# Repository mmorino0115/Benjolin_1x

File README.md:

# Benjolin_1x
Benjolin_1x KiCAD data. I designed this PCB based on the schematics of forestcaver's Benjolin 1.6. Then added some additional ideas from Jolin Lab's BE2N. I am really grateful to Rob Hordijk, who designed the original Benjolin. Following the original Benjolin design intent, this PCB is for personal, non-commercial use only.

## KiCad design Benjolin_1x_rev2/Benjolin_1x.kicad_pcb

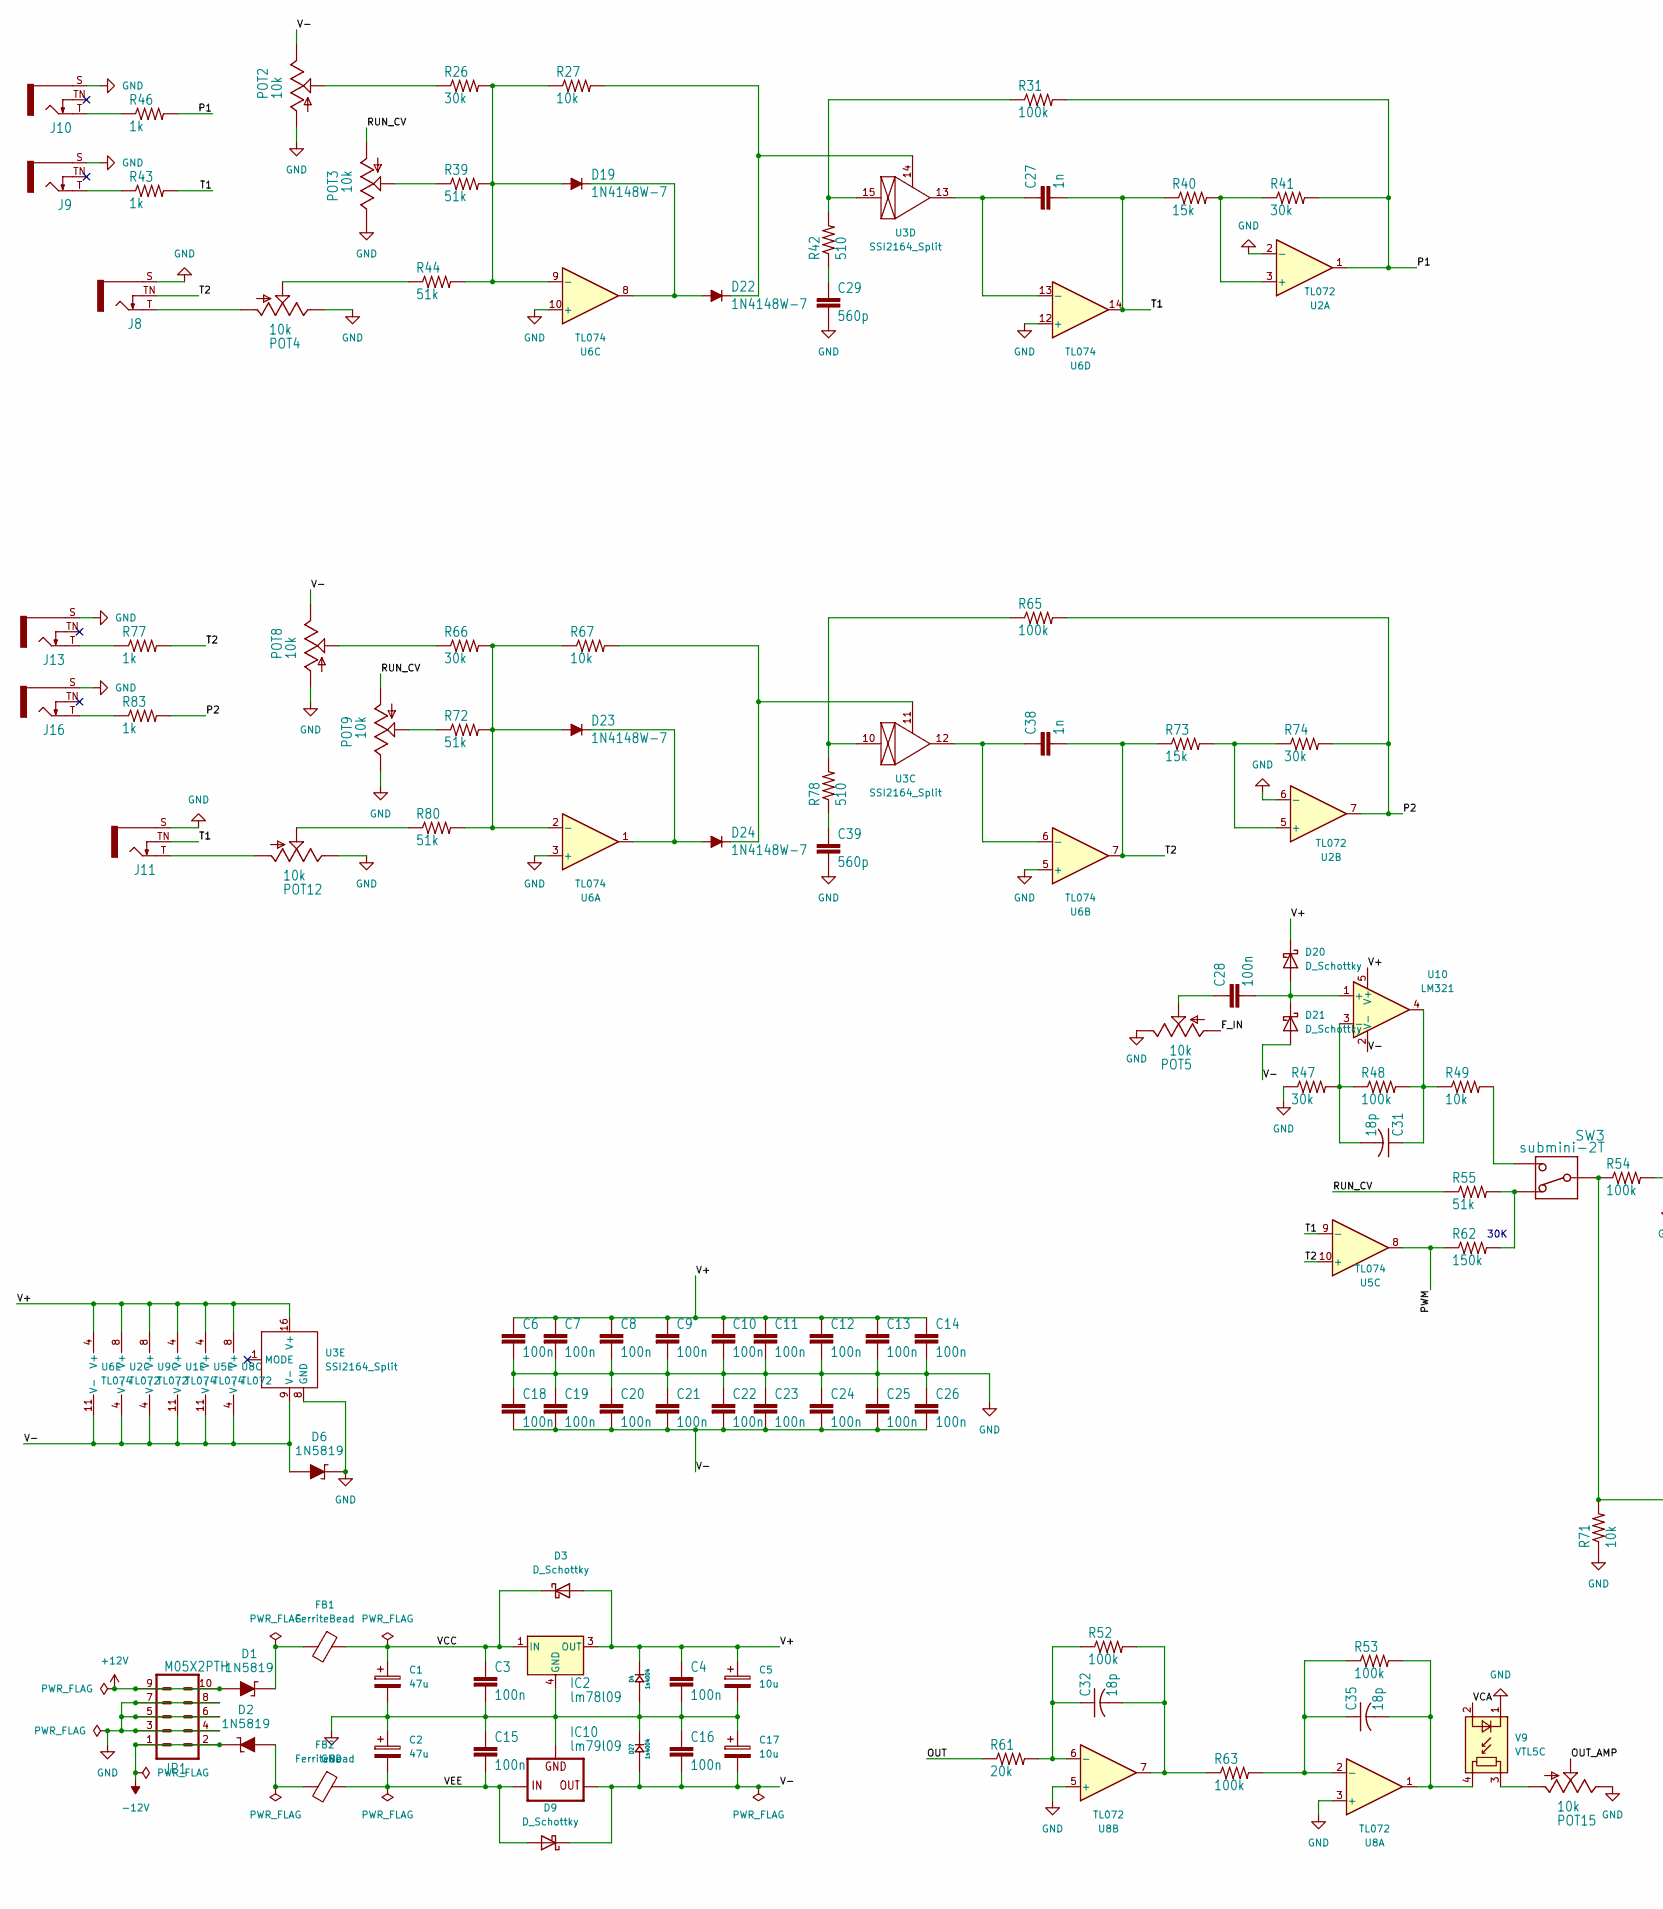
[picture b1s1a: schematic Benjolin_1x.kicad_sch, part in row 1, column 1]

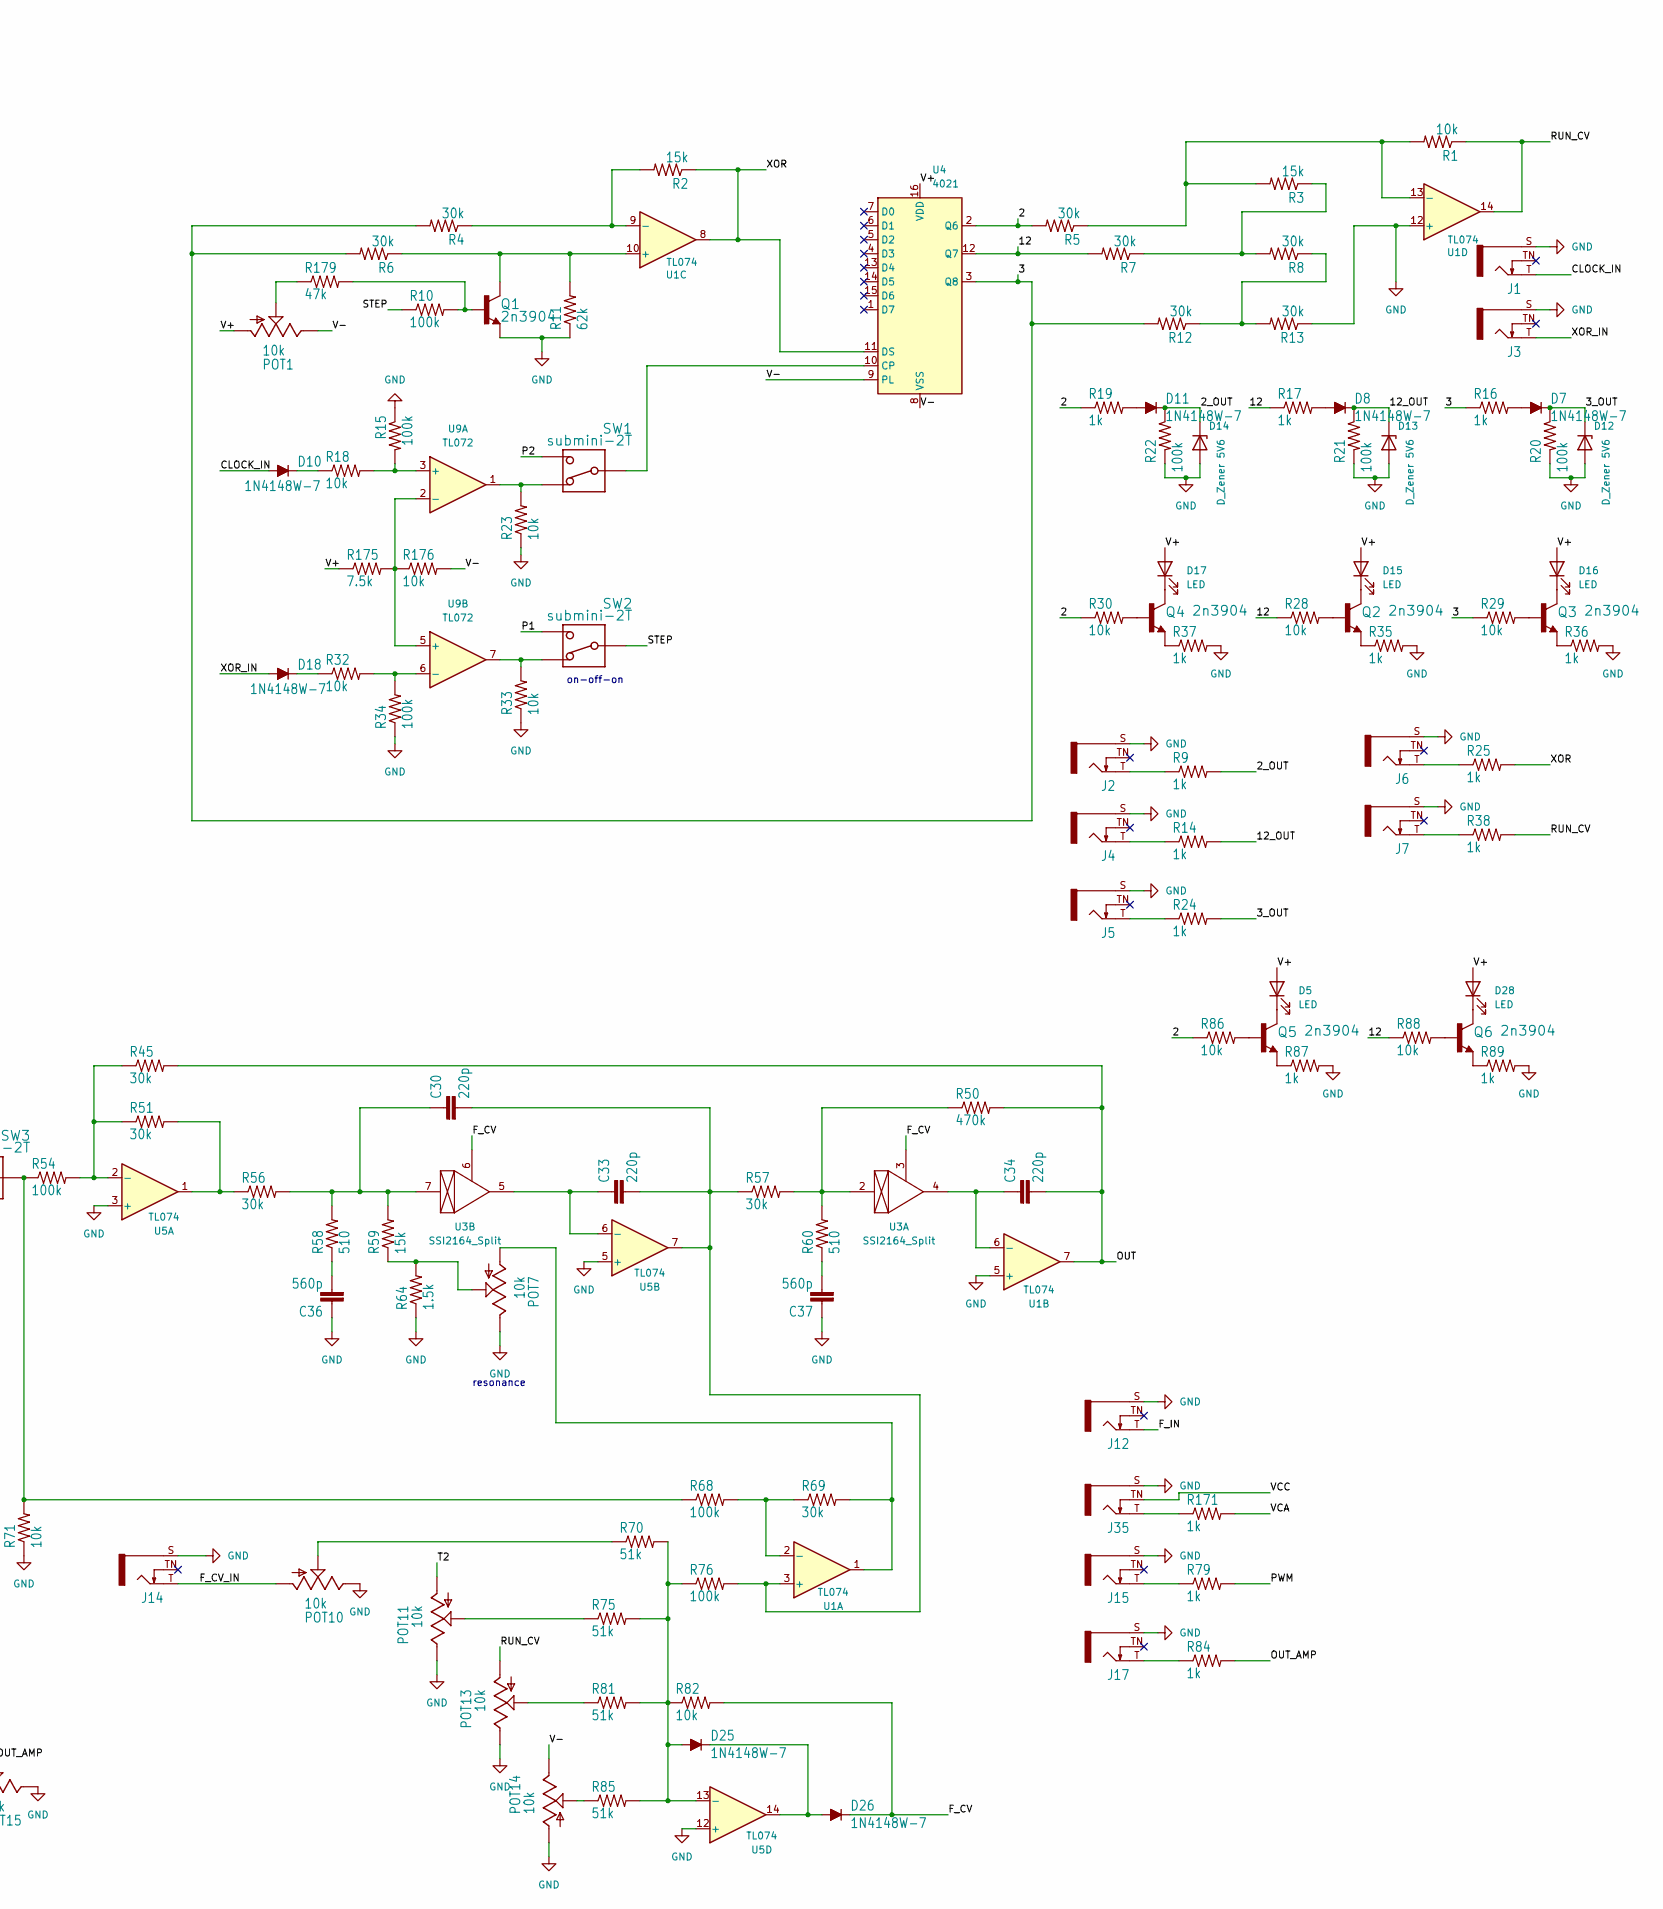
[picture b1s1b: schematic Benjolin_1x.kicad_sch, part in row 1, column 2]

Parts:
C1, C2: 47u; CP_Elec_5x4.5
C3, C4, C6, C7, C8, C9, C10, C11, C12, C13, C14, C15, C16, C18, C19, C20, C21, C22, C23, C24, C25, C26, C28: 100n; C_0603_1608Metric_Pad1.08x0.95mm_HandSolder
C5, C17: 10u; CP_Elec_4x5.4
C27, C38: 1n; C_0603_1608Metric_Pad1.08x0.95mm_HandSolder
C29, C36, C37, C39: 560p; C_0603_1608Metric_Pad1.08x0.95mm_HandSolder
C30, C33, C34: 220p; C_0603_1608Metric_Pad1.08x0.95mm_HandSolder
C31, C32, C35: 18p; C_0603_1608Metric_Pad1.08x0.95mm_HandSolder
D1, D2, D6: 1N5819; SOD-123; MPN 1N5819; Digi-Key_PN 1N5819FSCT-ND
D3, D9, D20, D21: D_Schottky; D_SMA
D4, D27: 1n4004; D_SMA_Handsoldering
D5, D15, D16, D17, D28: LED; LED_D3.0mm
D7, D8, D10, D11, D18, D19, D22, D23, D24, D25, D26: 1N4148W-7; D_SOD-123F
D12, D13, D14: D_Zener 5V6; D_MiniMELF_Handsoldering
FB1, FB2: FerriteBead; L_0603_1608Metric
IC2: lm78l09; TO-252-3
IC10: lm79l09; SOT-89-3
J1, J2, J3, J4, J5, J6, J7, J8, J9, J10, J11, J12, J13, J14, J15, J16, J17, J35: PJ301_THONKICONN6; AudioJack_3.5mm
JP1: M05X2PTH; IDC-Header_2x05_P2.54mm_Vertical
POT1, POT2, POT3, POT4, POT5, POT7, POT8, POT9, POT10, POT11, POT12, POT13, POT14, POT15: 10k; Potentiometer_Alps_RK09K_Single_Vertical
Q1, Q2, Q3, Q4, Q5, Q6: 2n3904; SOT-23-3
R1, R18, R23, R27, R28, R29, R30, R32, R33, R49, R67, R71, R82, R86, R88, R176: 10k; R_0603_1608Metric_Pad0.98x0.95mm_HandSolder
R2, R3, R40, R59, R73: 15k; R_0603_1608Metric_Pad0.98x0.95mm_HandSolder
R4, R5, R6, R7, R8, R12, R13, R26, R41, R45, R47, R51, R56, R57, R66, R69, R74: 30k; R_0603_1608Metric_Pad0.98x0.95mm_HandSolder
R9, R14, R16, R17, R19, R24, R25, R35, R36, R37, R38, R43, R46, R77, R79, R83, R84, R87, R89, R171: 1k; R_0603_1608Metric_Pad0.98x0.95mm_HandSolder
R10, R15, R20, R21, R22, R31, R34, R48, R52, R53, R54, R63, R65, R68, R76: 100k; R_0603_1608Metric_Pad0.98x0.95mm_HandSolder
R11: 62k; R_0603_1608Metric_Pad0.98x0.95mm_HandSolder
R39, R44, R55, R70, R72, R75, R80, R81, R85: 51k; R_0603_1608Metric_Pad0.98x0.95mm_HandSolder
R42, R58, R60, R78: 510; R_0603_1608Metric_Pad0.98x0.95mm_HandSolder
R50: 470k; R_0603_1608Metric_Pad0.98x0.95mm_HandSolder
R61: 20k; R_0603_1608Metric_Pad0.98x0.95mm_HandSolder
R62: 150k; R_0603_1608Metric_Pad0.98x0.95mm_HandSolder
R64: 1.5k; R_0603_1608Metric_Pad0.98x0.95mm_HandSolder
R175: 7.5k; R_0603_1608Metric_Pad0.98x0.95mm_HandSolder
R179: 47k; R_0603_1608Metric_Pad0.98x0.95mm_HandSolder
SW1, SW2, SW3: submini-2T; SPDT
U1, U5, U6: TL074; TSSOP-14_4.4x5mm_P0.65mm
U2, U8, U9: TL072; TSSOP-8_4.4x3mm_P0.65mm
U3: SSI2164_Split; SOIC-16_3.9x9.9mm_P1.27mm
U4: 4021; SOIC-16_3.9x9.9mm_P1.27mm
U10: LM321; SOT-23-5
V9: VTL5C; PerkinElmer_VTL5C

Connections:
+12V: D1.A, JP1.9, JP1.10
-12V: D2.K, JP1.1, JP1.2
/2: R5.2, R19.1, R30.1, R86.1, U4.2 (Q6)
/2_OUT: D11.1, D14.1 (K), R9.2, R22.1
/3: R4.2, R6.2, R12.2, R16.1, R29.1, U4.3 (Q8)
/3_OUT: D7.1, D12.1 (K), R20.1, R24.2
/12: R7.2, R17.1, R28.1, R88.1, U4.12 (Q7)
/12_OUT: D8.1, D13.1 (K), R14.2, R21.1
/CLOCK_IN: D10.2, J1.T
/F_CV: D26.1, R82.2, U3.3, U3.6
/F_CV_IN: J14.T, POT10.3
/F_IN: J12.T, POT5.3
/OUT: C34.2, R45.2, R50.2, R61.1, U1.7
/OUT_AMP: POT15.2, R84.2
/P1: R31.2, R41.2, R46.2, SW2.1, U2.1
/P2: R65.2, R74.2, R83.2, SW1.1, U2.7
/PWM: R62.1, R79.2, U5.8
/RUN_CV: POT3.3, POT9.3, POT13.3, R1.1, R38.2, R55.1, U1.14
/STEP: R10.1, SW2.2
/T1: C27.2, J11.TN, R40.1, R43.2, U5.9 (-), U6.14
/T2: C38.2, J8.TN, POT11.3, R73.1, R77.2, U5.10 (+), U6.7
/V+: C4.1, C5.1, C6.1, C7.1, C8.1, C9.1, C10.1, C11.1, C12.1, C13.1, C14.1, D3.2 (A), D4.2 (-), D5.2 (A), D15.2 (A), D16.2 (A), D17.2 (A), D20.1 (K), D28.2 (A), IC2.3 (OUT), POT1.3, R175.1, U1.4 (V+), U2.8 (V+), U3.16 (V+), U4.16 (VDD), U5.4 (V+), U6.4 (V+), U8.8 (V+), U9.8 (V+), U10.5 (V+)
/V-: C16.2, C17.2, C18.2, C19.2, C20.2, C21.2, C22.2, C23.2, C24.2, C25.2, C26.2, D6.A, D9.1 (K), D21.2 (A), D27.1 (+), IC10.3 (OUT), POT1.1, POT2.1, POT8.1, POT14.1, R176.2, U1.11 (V-), U2.4 (V-), U3.9 (V-), U4.8 (VSS), U4.9 (PL), U5.11 (V-), U6.11 (V-), U8.4 (V-), U9.4 (V-), U10.2 (V-)
/VCA: R171.2, V9.2 (+)
/VCC: C1.1, C3.1, D3.1 (K), FB1.1, IC2.1 (IN), J35.TN
/VEE: C2.2, C15.2, D9.2 (A), FB2.1, IC10.2
/XOR: R2.1, R25.2, U1.8, U4.11 (DS)
/XOR_IN: D18.2, J3.T
GND: C1.2, C2.1, C3.2, C4.2, C5.2, C6.2, C7.2, C8.2, C9.2, C10.2, C11.2, C12.2, C13.2, C14.2, C15.1, C16.1, C17.1, C18.1, C19.1, C20.1, C21.1, C22.1, C23.1, C24.1, C25.1, C26.1, C29.2, C36.1, C37.1, C39.2, D4.1 (+), D6.K, D12.2 (A), D13.2 (A), D14.2 (A), D27.2 (-), IC2.4 (GND), IC10.1 (GND), J1.S, J2.S, J3.S, J4.S, J5.S, J6.S, J7.S, J8.S, J9.S, J10.S, J11.S, J12.S, J13.S, J14.S, J15.S, J16.S, J17.S, J35.S, JP1.3, JP1.4, JP1.5, JP1.6, JP1.7, JP1.8, POT2.3, POT3.1, POT4.1, POT5.1, POT7.1, POT8.3, POT9.1, POT10.1, POT11.1, POT12.1, POT13.1, POT14.3, POT15.1, Q1.2 (E), R11.1, R13.1, R15.1, R20.2, R21.2, R22.2, R23.1, R33.1, R34.1, R35.2, R36.2, R37.2, R47.1, R64.1, R71.1, R87.2, R89.2, U1.5 (+), U1.12 (+), U2.2 (-), U2.6 (-), U3.8 (GND), U5.3 (+), U5.5 (+), U5.12 (+), U6.3 (+), U6.5 (+), U6.10 (+), U6.12 (+), U8.3 (+), U8.5 (+), V9.1 (-)
unnamed: C28.1, POT5.2
unnamed: C29.1, R42.1
unnamed: C30.1, R56.2, R58.2, R59.2, U3.7
unnamed: C31.1, R48.2, R49.1, U10.4
unnamed: C32.2, R52.2, R63.1, U8.7
unnamed: C35.2, R53.2, U8.1, V9.4
unnamed: C36.2, R58.1
unnamed: C37.2, R60.1
unnamed: C39.1, R78.1
unnamed: D1.K, FB1.2
unnamed: D2.A, FB2.2
unnamed: D5.1 (K), Q5.3 (C)
unnamed: D7.2, R16.2
unnamed: D8.2, R17.2
unnamed: D10.1, R18.1
unnamed: D11.2, R19.2
unnamed: D15.1 (K), Q2.3 (C)
unnamed: D16.1 (K), Q3.3 (C)
unnamed: D17.1 (K), Q4.3 (C)
unnamed: D18.1, R32.1
unnamed: D19.1, D22.2, U6.8
unnamed: C28.2, D20.2 (A), D21.1 (K), U10.1 (+)
unnamed: D22.1, R27.2, U3.14
unnamed: D23.1, D24.2, U6.1
unnamed: D24.1, R67.2, U3.11
unnamed: D25.1, D26.2, U5.14
unnamed: D28.1 (K), Q6.3 (C)
unnamed: J2.T, R9.1
unnamed: J4.T, R14.1
unnamed: J5.T, R24.1
unnamed: J6.T, R25.1
unnamed: J7.T, R38.1
unnamed: J8.T, POT4.3
unnamed: J9.T, R43.1
unnamed: J10.T, R46.1
unnamed: J11.T, POT12.3
unnamed: J13.T, R77.1
unnamed: J15.T, R79.1
unnamed: J16.T, R83.1
unnamed: J17.T, R84.1
unnamed: J35.T, R171.1
unnamed: POT1.2, R179.1
unnamed: POT2.2, R26.1
unnamed: POT3.2, R39.1
unnamed: POT4.2, R44.1
unnamed: POT7.2, R59.1, R64.2
unnamed: POT7.3, R69.2, U1.1
unnamed: POT8.2, R66.1
unnamed: POT9.2, R72.1
unnamed: POT10.2, R70.1
unnamed: POT11.2, R75.1
unnamed: POT12.2, R80.1
unnamed: POT13.2, R81.1
unnamed: POT14.2, R85.1
unnamed: POT15.3, V9.3
unnamed: Q1.1 (B), R10.2, R179.2
unnamed: Q1.3 (C), R6.1, R11.2, U1.10 (+)
unnamed: Q2.1 (B), R28.2
unnamed: Q2.2 (E), R35.1
unnamed: Q3.1 (B), R29.2
unnamed: Q3.2 (E), R36.1
unnamed: Q4.1 (B), R30.2
unnamed: Q4.2 (E), R37.1
unnamed: Q5.1 (B), R86.2
unnamed: Q5.2 (E), R87.1
unnamed: Q6.1 (B), R88.2
unnamed: Q6.2 (E), R89.1
unnamed: R3.1, R7.1, R8.2
unnamed: R8.1, R12.1, R13.2
unnamed: R23.2, SW1.3, U9.1
unnamed: R31.1, R42.2, U3.15
unnamed: R33.2, SW2.3, U9.7
unnamed: R49.2, SW3.1
unnamed: R50.1, R57.2, R60.2, U3.2
unnamed: R51.2, R56.1, U5.1
unnamed: R54.1, R68.1, R71.2, SW3.2
unnamed: R55.2, R62.2, SW3.3
unnamed: R65.1, R78.2, U3.10
unnamed: C30.2, C33.2, R57.1, R76.2, U1.3 (+), U5.7
unnamed: R68.2, R69.1, U1.2 (-)
unnamed: C34.1, U1.6 (-), U3.4
unnamed: R2.2, R4.1, U1.9 (-)
unnamed: R1.2, R3.2, R5.1, U1.13 (-)
unnamed: R40.2, R41.1, U2.3 (+)
unnamed: R73.2, R74.1, U2.5 (+)
unnamed: SW1.2, U4.10 (CP)
unnamed: R45.1, R51.1, R54.2, U5.2 (-)
unnamed: C33.1, U3.5, U5.6 (-)
unnamed: D25.2, R70.2, R75.2, R76.1, R81.2, R82.1, R85.2, U5.13 (-)
unnamed: D23.2, R66.2, R67.1, R72.2, R80.2, U6.2 (-)
unnamed: C38.1, U3.12, U6.6 (-)
unnamed: D19.2, R26.2, R27.1, R39.2, R44.2, U6.9 (-)
unnamed: C27.1, U3.13, U6.13 (-)
unnamed: C35.1, R53.1, R63.2, U8.2 (-)
unnamed: C32.1, R52.1, R61.2, U8.6 (-)
unnamed: R15.2, R18.2, U9.3 (+)
unnamed: R175.2, R176.1, U9.2 (-), U9.5 (+)
unnamed: R32.2, R34.2, U9.6 (-)
unnamed: C31.2, R47.2, R48.1, U10.3 (-)

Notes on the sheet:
on-off-on
resonance
30K

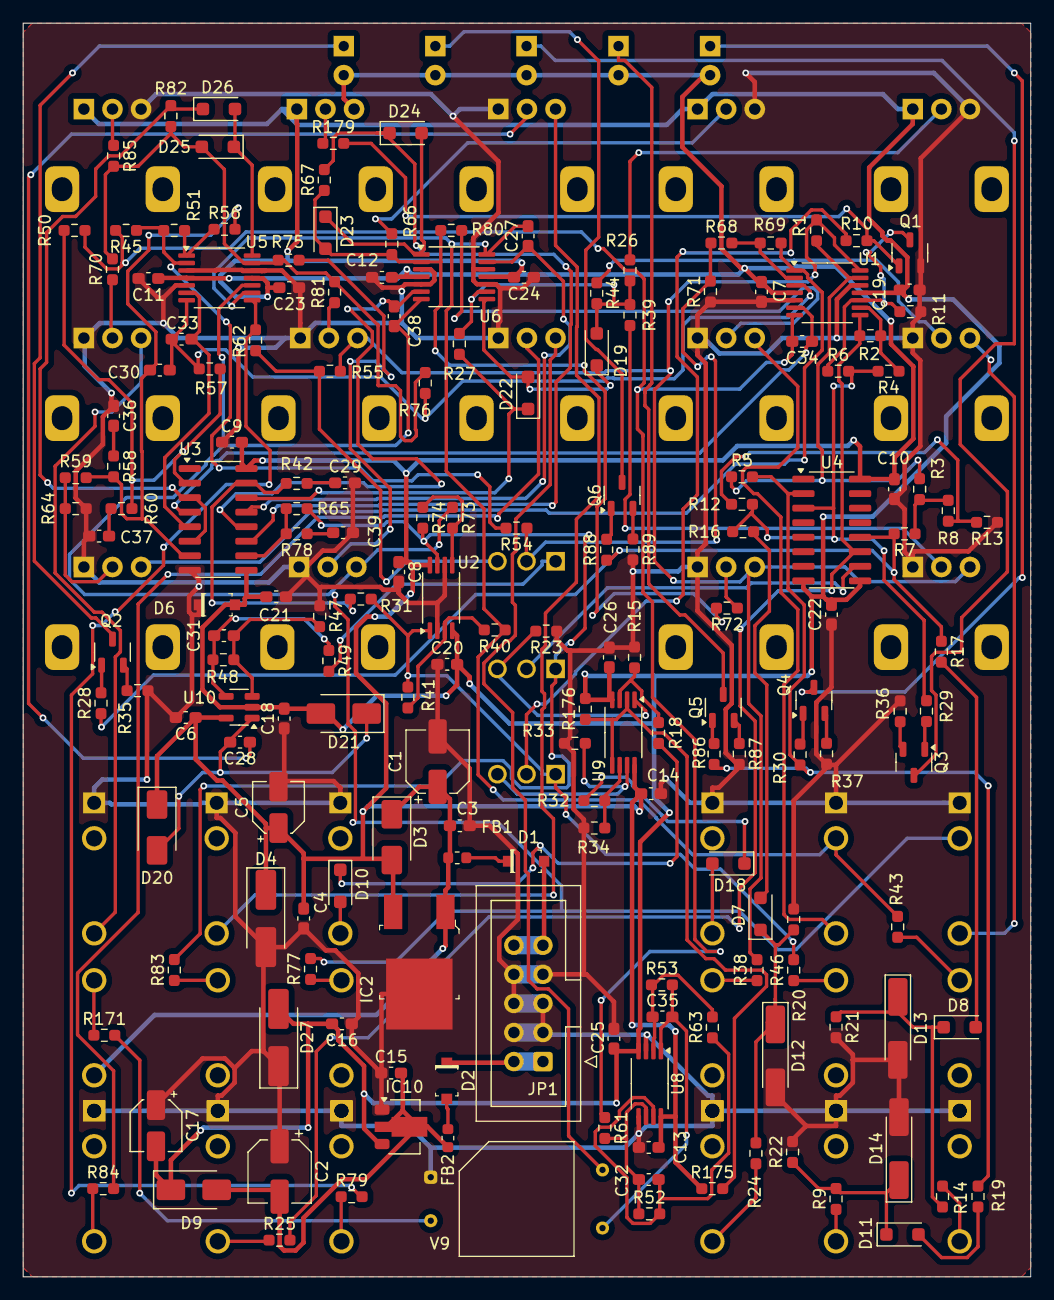
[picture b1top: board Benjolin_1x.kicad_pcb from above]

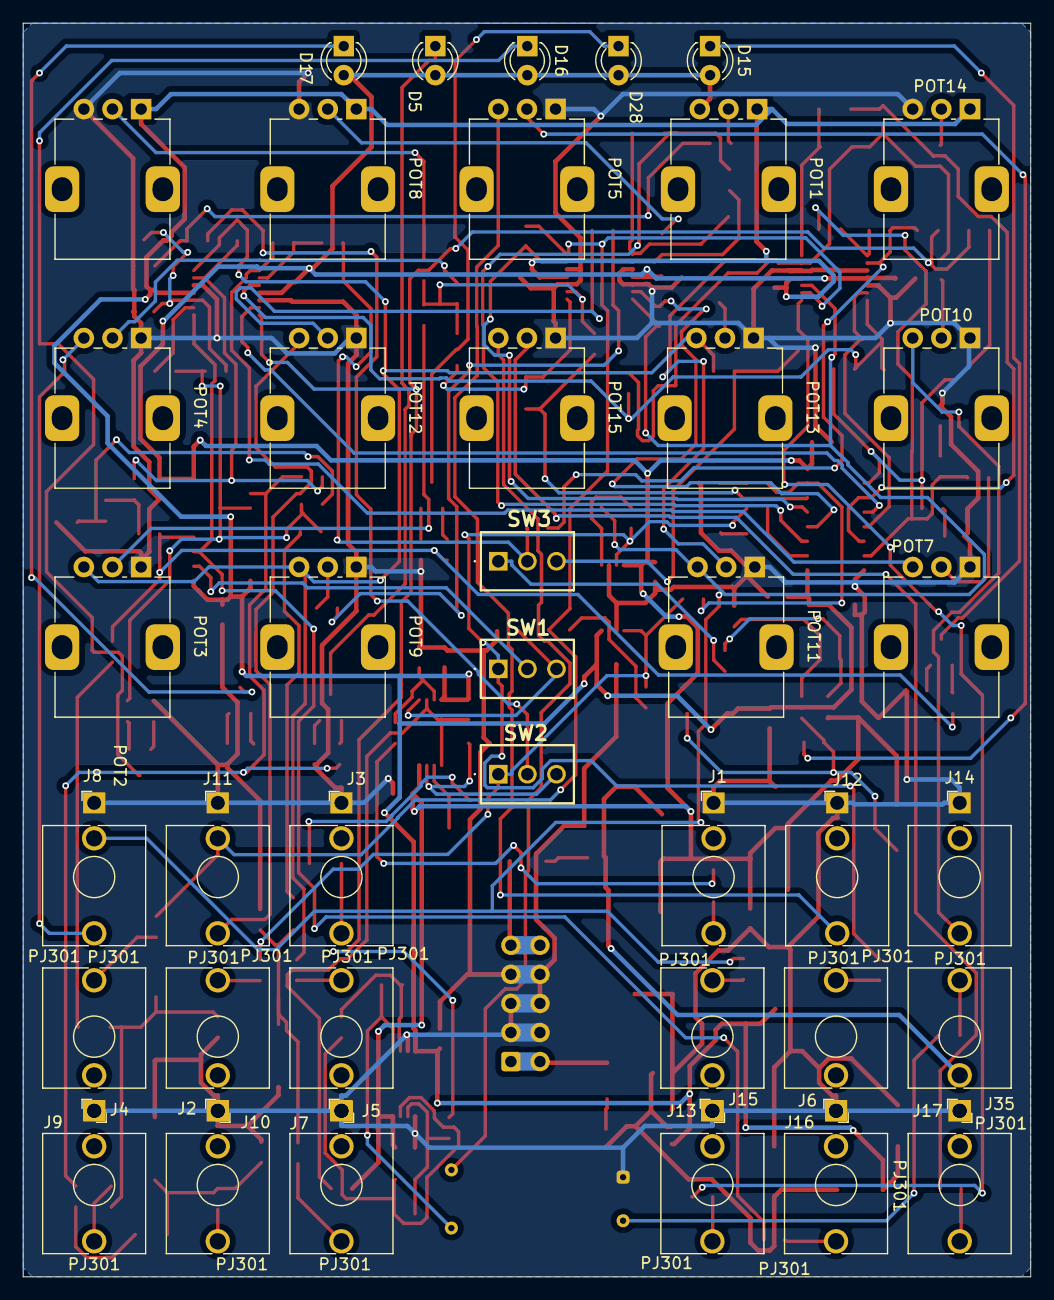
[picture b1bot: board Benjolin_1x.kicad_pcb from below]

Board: 2 copper layers, 88.0 x 109.5 mm, 216 parts (40 on the bottom side), 128 nets.

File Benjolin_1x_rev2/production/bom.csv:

Designator,Footprint,Quantity,Value,LCSC Part #
"C1, C2",CP_Elec_5x4.5,2,47u,
"C10, C11, C12, C13, C14, C15, C16, C18, C19, C20, C21, C22, C23, C24, C25, C26, C28, C3, C4, C6, C7, C8, C9",0603,23,100n,
"C17, C5",CP_Elec_4x5.4,2,10u,
"C27, C38",0603,2,1n,
"C29, C36, C37, C39",0603,4,560p,
"C30, C33, C34",0603,3,220p,
"C31, C32, C35",0603,3,18p,
"D1, D2, D6",SOD-123,3,1N5819,1N5819
"D10, D11, D18, D19, D22, D23, D24, D25, D26, D7, D8",D_SOD-123F,11,1N4148W-7,
"D12, D13, D14",D_MiniMELF_Handsoldering,3,D_Zener 5V6,
"D15, D16, D17, D28, D5",LED_D3.0mm,5,LED,
"D20, D21, D3, D9",D_SMA,4,D_Schottky,
"D27, D4",D_SMA_Handsoldering,2,1n4004,
"FB1, FB2",0603,2,FerriteBead,
IC10,SOT-89-3,1,lm79l09,
IC2,TO-252-3,1,lm78l09,
"J1, J10, J11, J12, J13, J14, J15, J16, J17, J2, J3, J35, J4, J5, J6, J7, J8, J9",AudioJack_3.5mm,18,PJ301,
JP1,IDC-Header_2x05_P2.54mm_Vertical,1,M05X2PTH,
"POT1, POT10, POT11, POT12, POT13, POT14, POT15, POT2, POT3, POT4, POT5, POT7, POT8, POT9",Potentiometer_Alps_RK09K_Single_Vertical,14,10k,
"Q1, Q2, Q3, Q4, Q5, Q6",SOT-23-3,6,2n3904,
"R1, R176, R18, R23, R27, R28, R29, R30, R32, R33, R49, R67, R71, R82, R86, R88",0603,16,10k,
"R10, R15, R20, R21, R22, R31, R34, R48, R52, R53, R54, R63, R65, R68, R76",0603,15,100k,
R11,0603,1,62k,
"R12, R13, R26, R4, R41, R45, R47, R5, R51, R56, R57, R6, R66, R69, R7, R74, R8",0603,17,30k,
"R14, R16, R17, R171, R19, R24, R25, R35, R36, R37, R38, R43, R46, R77, R79, R83, R84, R87, R89, R9",0603,20,1k,
R175,0603,1,7.5k,
R179,0603,1,47k,
"R2, R3, R40, R59, R73",0603,5,15k,
"R39, R44, R55, R70, R72, R75, R80, R81, R85",0603,9,51k,
"R42, R58, R60, R78",0603,4,510,
R50,0603,1,470k,
R61,0603,1,20k,
R62,0603,1,150k,
R64,0603,1,1.5k,
"SW1, SW2, SW3",2MS3T1B3M2QES,3,submini-2T,
"U1, U5, U6",TSSOP-14_4.4x5mm_P0.65mm,3,TL074,
U10,SOT-23-5,1,LM321,
"U2, U8, U9",TSSOP-8_4.4x3mm_P0.65mm,3,TL072,
U3,SOIC-16_3.9x9.9mm_P1.27mm,1,SSI2164_Split,
U4,SOIC-16_3.9x9.9mm_P1.27mm,1,4021,
V9,PerkinElmer_VTL5C,1,VTL5C,

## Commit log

2026-01-22 Create note
2026-01-22 Rename note to building_note
